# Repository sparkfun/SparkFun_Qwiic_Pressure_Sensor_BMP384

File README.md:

SparkFun Pressure Sensor - BMP384 (Qwiic) 
=========================================

<table class="table table-hover table-striped table-bordered">
  <tr align="center">
    <td></td>
    <td></td>
  </tr>
  <tr align="center">
    <td><a href="https://www.sparkfun.com/products/19662"><i>SparkFun Pressure Sensor - BMP384 (Qwiic)</i></a></td>
    <td><a href="https://www.sparkfun.com/products/19833"><i>SparkFun Micro Pressure Sensor - BMP384 (Qwiic)</i></a></td>
  </tr>
</table>

The SparkFun Pressure Sensor - BMP384 (Qwiic) and Micro Pressure Sensor - BMP384 (Qwiic) feature the BMP384 pressure sensor from Bosch. he BMP384 excels at high-resolution measurements (up to 21-bit) and uses a gel-filled cavity to provide extra resistance to liquids (water and other chemicals) making it a great option for monitoring pressure in a wide variety of environments though the sensor is <i>not</i> water-proof.

Repository Contents
-------------------
* **/Documents** - Datasheet
* **/Hardware** - Eagle design files (.brd, .sch)
* **/Production** - Production panel files (.brd)

Documentation
-------------
* **[Hookup Guide](https://learn.sparkfun.com/tutorials/qwiic-pressure-sensor-bmp384-hookup-guide)** - Basic Hookup Guide for the SparkFun Pressure Sensor - BMP384 (Qwiic)
* **[BMP384 Arduino Library](https://github.com/sparkfun/SparkFun_BMP384_Arduino_Library)** - Arduino library for the BMP384 based off the Bosch API.

Product Versions
----------------
* [SEN-19662](https://www.sparkfun.com/products/19662) - Standard Size Initial Release.
* [SEN-19833](https://www.sparkfun.com/products/19833) - Micro Size Initial Release.

License Information
-------------------

This product is _**open source**_! 

Please review the LICENSE.md file for license information.

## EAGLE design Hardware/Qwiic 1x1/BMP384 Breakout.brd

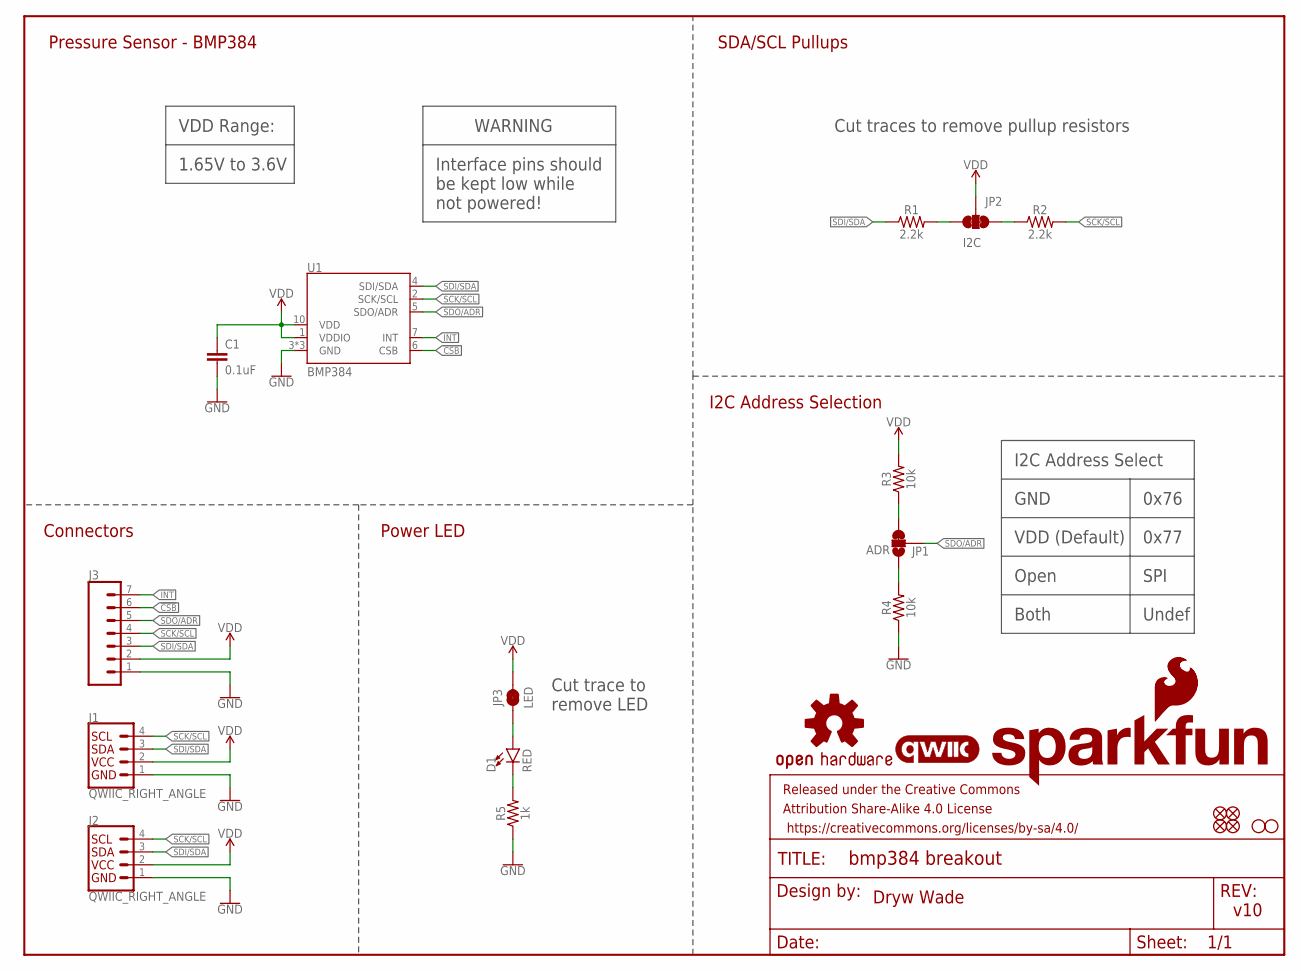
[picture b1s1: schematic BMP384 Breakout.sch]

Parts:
C1: 0.1uF; 0603
D1: RED; LED-0603
FD1, FD2, FD3, FD4: FIDUCIAL1X2; FIDUCIAL-1X2
FRAME1: FRAME-LETTER; CREATIVE_COMMONS
H1, H2: STAND-OFF
J1, J2: QWIIC_RIGHT_ANGLE; JST04_1MM_RA
J3: CONN_07NO_SILK; 1X07_NO_SILK
JP1: ADR; SMT-JUMPER_3_1-NC_TRACE_SILK
JP2: I2C; SMT-JUMPER_3_2-NC_TRACE_SILK
JP3: LED; SMT-JUMPER_2_NC_TRACE_SILK
LOGO1: OSHW-LOGOS; OSHW-LOGO-S
LOGO2: SFE_LOGO_FLAME.2_INCH; SFE_LOGO_FLAME_.2
LOGO3: QWIIC_LOGO_5MM; QWIIC_5MM
LOGO4: SFE_LOGO_NAME_FLAME.1_INCH; SFE_LOGO_NAME_FLAME_.1
R1, R2: 2.2k; 0603
R3, R4: 10k; 0603
R5: 1k; 0603
U1: BMP384; LGA-10

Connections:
!CSB!: J3.6, U1.6 (CSB)
GND: C1.2, J1.1, J2.1, J3.1, R4.1, R5.1, U1.3 (GND), U1.8 (GND), U1.9 (GND)
INT: J3.7, U1.7 (INT)
unnamed: JP1.3, R3.1
unnamed: JP1.1, R4.2
unnamed: JP2.1, R2.1
unnamed: JP2.3, R1.2
unnamed: D1.A, JP3.1
unnamed: D1.C, R5.2
SCK/SCL: J1.4, J2.4, J3.4, R2.2, U1.2 (SCK/SCL)
SDI/SDA: J1.3, J2.3, J3.3, R1.1, U1.4 (SDI/SDA)
SDO/ADR: J3.5, JP1.2, U1.5 (SDO/ADR)
VDD: C1.1, J1.2, J2.2, J3.2, JP2.2, JP3.2, R3.2, U1.1 (VDDIO), U1.10 (VDD)

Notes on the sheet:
Dryw Wade
v10
Connectors
Pressure Sensor - BMP384
I2C Address Selection
I2C Address Select
GND
VDD (Default)
0x76
0x77
Open
Both
SPI
Undef
SDA/SCL Pullups
Cut traces to remove pullup resistors
VDD Range:
1.65V to 3.6V
Power LED
WARNING
Interface pins should be kept low while not powered!
Cut trace to remove LED

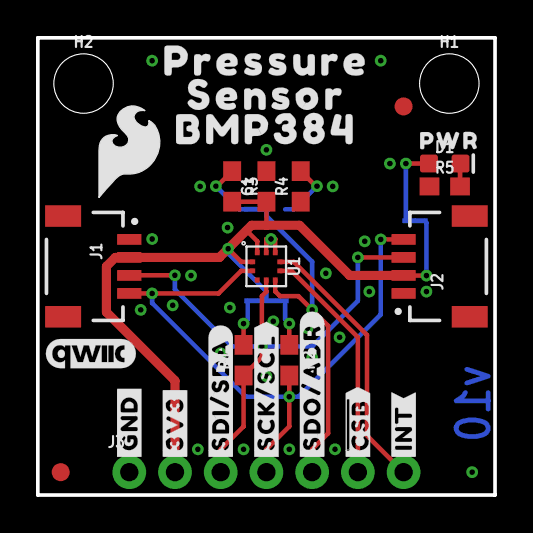
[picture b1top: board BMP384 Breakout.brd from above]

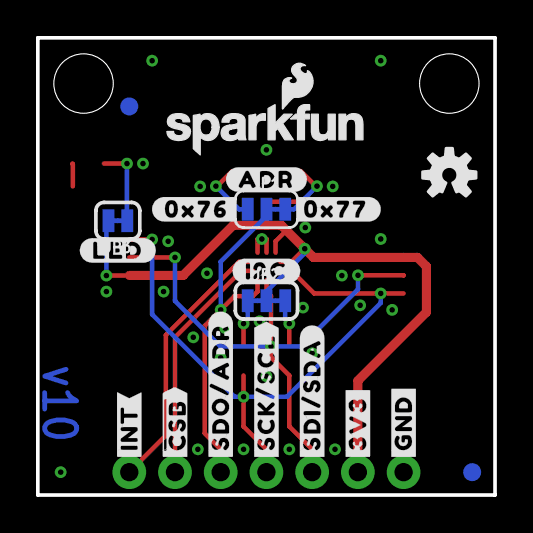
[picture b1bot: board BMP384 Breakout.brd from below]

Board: 2 copper layers, 25.4 x 25.4 mm, 48 parts (19 on the bottom side), 13 nets.

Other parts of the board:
U$1, U$2: #GND#0
U$3, U$20: #3V3#0
U$4: #I2C#0
U$5, U$6: #SDI#SDA#0
U$7, U$8: #SCK#SCL#0
U$9, U$10: #SDO#ADR#0
U$11: #0X76#0
U$12: #0X77#0
U$13, U$14: #INT#0
U$15: PWR0
U$17: #ADR#0
U$19: #LED#0
U$21: PRESSURE0
U$25, U$28: ##CSB##0
U$26: SENSOR0
U$27: BMP3840

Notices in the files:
parts and their libraries:
SparkFun-Aesthetics: Licensing: Creative Commons ShareAlike 4.0 International - https://creativecommons.org/licenses/by-sa/4.0
SparkFun-Aesthetics: Released under the Creative Commons Attribution Share-Alike 4.0 License
SparkFun-Aesthetics: https://creativecommons.org/licenses/by-sa/4.0
